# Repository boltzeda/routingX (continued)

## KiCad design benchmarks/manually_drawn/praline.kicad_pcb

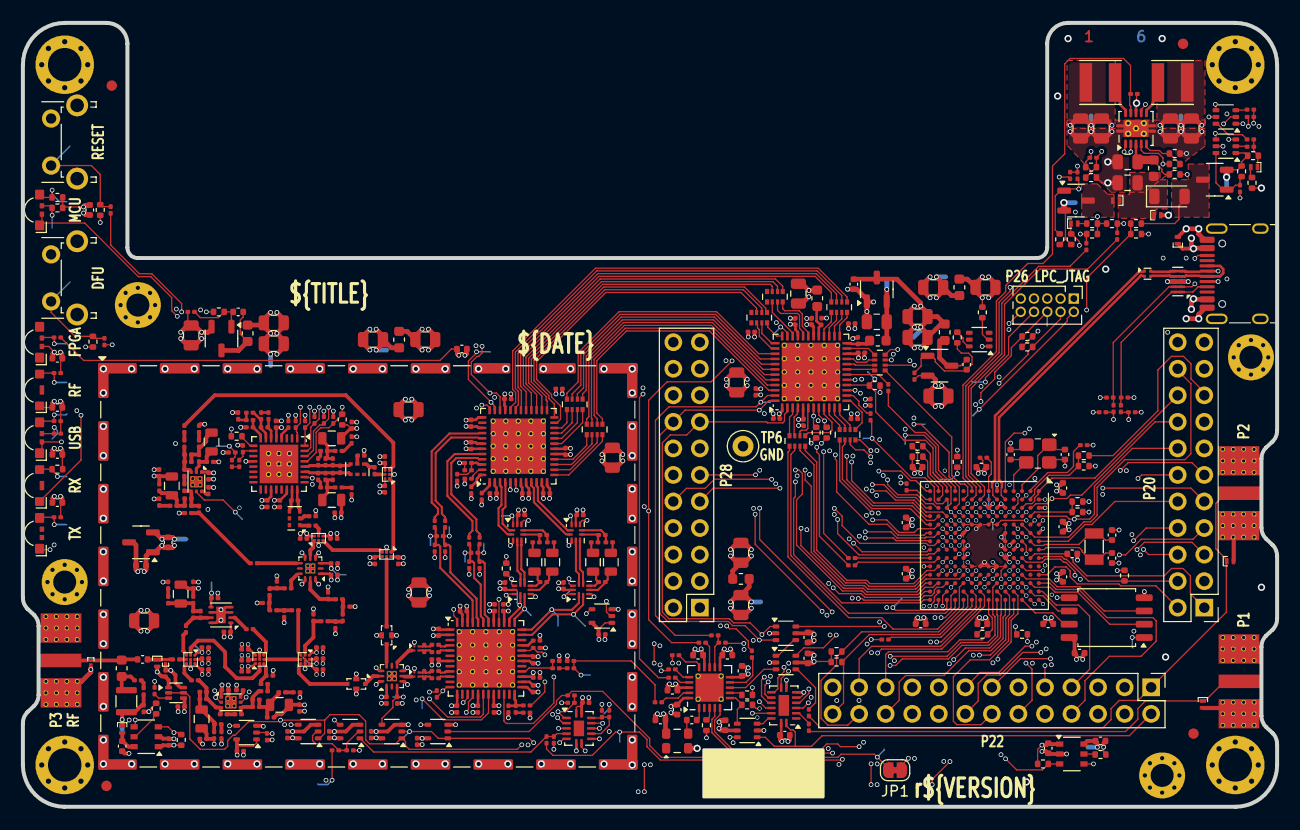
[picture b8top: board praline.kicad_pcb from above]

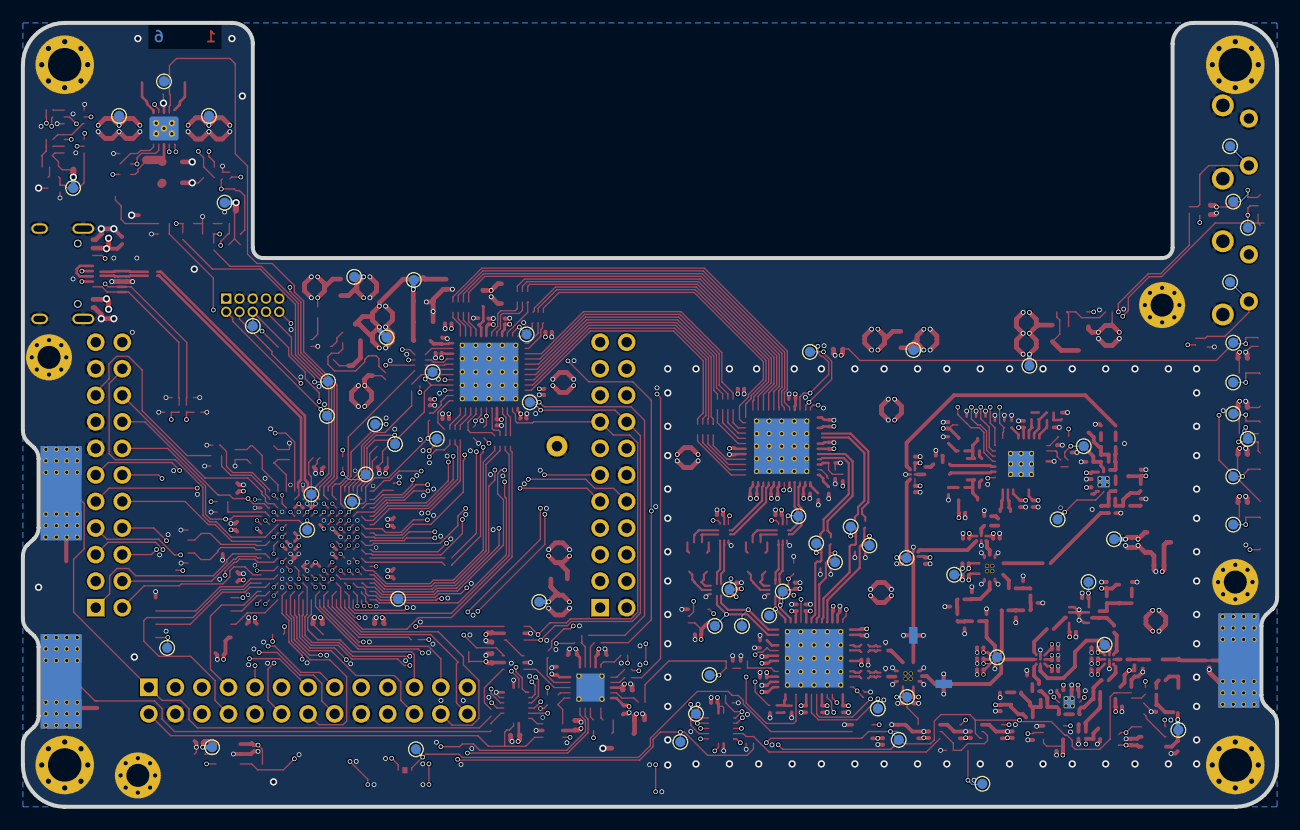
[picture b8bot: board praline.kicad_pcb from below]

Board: 6 copper layers, 120.0 x 75.0 mm, 581 parts (65 on the bottom side), 430 nets.

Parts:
C1, C2, C3, C5, C7, C8, C10, C17, C21, C24, C25, C26, C27, C28, C30, C31, C41, C42, C46, C48, C49, C50, C52, C53, C58, C59, C60, C62, C66, C68, C69, C71, C72, C73, C75, C77, C78, C79, C82, C83, C84, C85, C86, C87, C88, C89, C90, C92, C93, C94, C95, C97, C98, C100, C106, C123, C139, C141, C142, C148, C149, C150, C156, C159, C160, C161, C174, C176, C177, C178, C179, C183, C185, C187, C189, C190, C191, C192, C193, C194, C195, C196, C202, C203, C205, C206, C207, C208, C210, C211, C212: 1 uF; C_0201_0603Metric
C4, C6, C9, C11, C16, C18, C19, C20, C29, C55, C57, C63, C65: 3.3 nF; C_0201_0603Metric
C12, C13, C151, C152: 330 pF; C_0201_0603Metric
C14: 8.2 pF; C_0201_0603Metric
C15, C74, C76, C107, C108: 180 pF; C_0201_0603Metric
C22, C23, C32, C33, C39, C40, C43, C64, C80, C81, C110, C113, C119, C120, C121, C122, C124, C128, C129, C130, C131, C132, C133, C134, C135, C136, C137, C138, C140, C144, C162, C168, C171, C173, C199: 1 uF; C_0402_1005Metric
C34, C35, C36, C37, C67, C109, C125: 33 pF; C_0201_0603Metric
C44, C70, C112: 100 pF; C_0201_0603Metric
C45: 2.2 nF; C_0201_0603Metric
C47: 68 pF; C_0201_0603Metric
C51, C61, C101, C103, C198: 0.7 pF; C_0201_0603Metric
C54, C56: 1.8 pF; C_0201_0603Metric
C91, C96: 1.6 pF; C_0201_0603Metric
C99, C102, C115: 22 pF; C_0201_0603Metric
C104, C111: 4.3 pF; C_0201_0603Metric
C105, C117, C126, C127, C145, C146, C154, C163, C165, C166, C167, C169, C170, C172, C175, C181, C182, C184, C186, C197, C200, C201, C204: 10 uF; C_0805_2012Metric
C114, C188, C209: 0.3 pF; C_0201_0603Metric
C116: 47 pF; C_0201_0603Metric
C118, C157, C158, C164: 18 pF; C_0402_1005Metric
C143, C147: 22 uF; C_0805_2012Metric
C153, C155, C180: 100 nF; C_0402_1005Metric
D1: TVS; TSSLP-2-1
D2, D5: LED; LED_Single_Xinglight_XL-3210_Horizontal
D3, D9, D18: TVS; TSLP-2-19
D4, D6, D7, D8: LED; LED_Dual_Xinglight_XL-3210_Horizontal
D10: Schottky; TSLP-2-19
D11: 6.2 V; TSLP-2-19
D12: D; D_SOD-123FL
D13: 0; TSLP-2-19
D14: PIN; TSLP-2-19
D15: Schottky; TSSLP-2-1
D16, D17: 5.6 V; TSLP-2-19
FB1, FB2, FB3, FB4, FB5, FB6, FB7, FB8: Ferrite; L_0603_1608Metric
FID1, FID2, FID3, FID4: Fiducial_1mm_Mask2mm
FL1: CommonModeChoke; L_CommonModeChoke_Murata_DLM0NS
FL2, FL3: BPF; Filter_Pulse_BPF1608LM09R5000A
H1, H2, H3, H4: MountingHole_Pad; MountingHole_3.2mm_M3_Pad_Via
H5, H6, H7, H8: MountingHole_Pad; MountingHole_2.2mm_M2_Pad_Via
J1: USB_C; USB_C_Receptacle_HRO_TYPE-C-31-M-12
J3: RF_SHIELD_FRAME; Laird_Technologies_BMI-S-230-F_50.8x38.1mm
JP1: SolderJumper_2_Bridged; SolderJumper-2_P1.3mm_Bridged_RoundedPad1.0x1.5mm
L1, L7: DNP; L_0201_0603Metric
L2, L4, L5, L21, L22, L23, L24, L26, L27, L29, L33: 100 uH; L_TDK_MLZ2012_h1.25mm
L3, L12, L30, L31, L32: 56 nH; L_0201_0603Metric
L6, L14: 5.6 nH; L_0201_0603Metric
L8, L15: 4.7 nH; L_0201_0603Metric
L9: 10 nH; L_0201_0603Metric
L10, L11: 4.7 uH; L_Taiyo-Yuden_NR-40xx
L13: 2.2 uH; L_0603_1608Metric
L16, L17: 1.8 nH; L_0201_0603Metric
L18: 1.6 nH; L_0201_0603Metric
L19: 47 uH; L_Taiyo-Yuden_A251818
L28: 18 nH; L_0201_0603Metric
L34: 33 nH; L_0201_0603Metric
P1, P2, P3: SMA; SMA_MyAntenna_A-SMA-KE-16.5A_EdgeMount
P20, P28: HEADER_2x11; PinSocket_2x11_P2.54mm_Vertical_Flipped
P22: HEADER_2x13; PinSocket_2x13_P2.54mm_Vertical_Flipped
P26: LPC_JTAG; PinHeader_2x05_P1.27mm_Vertical
Q1: NMOS/PMOS; SOT-563
Q3, Q4, Q5, Q6: PMOS; SOT-23-3
Q7, Q10: 2NPN; SOT-363_SC-70-6
Q9: 2PNP; SOT-363_SC-70-6
R1, R2, R72, R115, R116, R117, R132, R137: 470; R_0201_0603Metric
R3, R11, R18, R61: 22.6k; R_0201_0603Metric
R4: 51k; R_0201_0603Metric
R5, R7, R36, R37, R40, R44, R48, R49, R50, R52, R59, R62, R63, R64, R66, R67, R68, R75, R85, R93, R100, R104, R105, R113, R120: 10k; R_0402_1005Metric
R6, R21, R29, R127, R140, R141, R143, R145, R148: 100; R_0201_0603Metric
R8, R9, R10, R13, R149, R150: 0; R_0201_0603Metric
R12, R19, R23, R30, R31, R32, R34, R41, R84, R108, R139, R142: 33; R_0201_0603Metric
R14, R15, R16, R17, R118, R119: DNP; R_0201_0603Metric
R20, R38, R46, R47, R55: 180k; R_0402_1005Metric
R22, R57, R81, R83, R86, R87: 33k; R_0201_0603Metric
R24, R35, R94, R96, R98, R114, R129, R133, R138, R144, R151, R153, R154: 1k; R_0201_0603Metric
R25: 750; R_0201_0603Metric
R26: 1.2k; R_0201_0603Metric
R27, R28, R45, R53: 1.8k; R_0402_1005Metric
R33, R123, R155: 10; R_0201_0603Metric
R39: 37.4k; R_0402_1005Metric
R42, R43, R124, R128, R130, R131, R136, R146, R147: 220; R_0201_0603Metric
R51, R54, R74, R76, R92, R95, R97, R99, R103, R106, R107, R109, R122, R126: 4.7k; R_0201_0603Metric
R56, R58, R70: 820k; R_0402_1005Metric
R60, R71, R79, R80: 5.1k; R_0402_1005Metric
R65, R82: 18k; R_0402_1005Metric
R69, R121, R125, R135: 12k; R_0201_0603Metric
R73: 3k; R_0402_1005Metric
R77, R78: 2.2k; R_0201_0603Metric
R88, R89, R90, R91: 18.7k; R_0402_1005Metric
R101: 100k; R_0402_1005Metric
R102, R110, R111, R112, R156, R157: 330; R_0201_0603Metric
R134: 180; R_0201_0603Metric
R152: 3; R_0201_0603Metric
RN1, RN2, RN3, RN4, RN5, RN6, RN7, RN8: 100; R_Array_Convex_4x0402
SW1, SW2: SWITCH; SW_Tactile_SPST_Angled_PTS645Vx58-2LFS
T1, T2: RF_BALUN; Anaren_0805_2012Metric-6
T3, T4: IF_BALUN; Balun_TDK_TFSZ06052460-3310A2X
TP1, TP2, TP3, TP4, TP5, TP7, TP8, TP9, TP10, TP11, TP12, TP13, TP14, TP15, TP16, TP17, TP18, TP19, TP20, TP21, TP22, TP23, TP24, TP25, TP26, TP27, TP28, TP29, TP30, TP31, TP32, TP33, TP34, TP35, TP36, TP37, TP38, TP39, TP40, TP41, TP42, TP43, TP44, TP45, TP46, TP47, TP48, TP49, TP50, TP51, TP52, TP53, TP54, TP55, TP56, TP57, TP58, TP59, TP60, TP61, TP62, TP63, TP64, TP65, TP66: TestPoint; TestPoint_Pad_D1.0mm
TP6: TestPoint; TestPoint_Loop_D1.80mm_Drill1.0mm_Beaded
U1, U2: MXD8546F; QFN-12-1EP_2x2mm_P0.5mm_EP1x1mm
U3, U8, U34, U35: GT4227; GTIC_UQFN-10_1.4x1.8mm_P0.4mm
U4: RFFC5072; QFN-32-1EP_5x5mm_P0.5mm_EP3.7x3.7mm_ThermalVias
U5, U6, U7: FM8625H; TSLP-6-4_1.1x0.7mm_P0.4mm
U9, U12, U14: MXD8638C
U10, U11, U13, U36: 74LVC1G86; SOT-353_SC-70-5
U15: TVS_USB; Diodes_UDFN-10_1.0x2.5mm_P0.5mm
U16: ICE40UP5K; QFN-48-1EP_7x7mm_P0.5mm_EP5.6x5.6mm_ThermalVias
U17: MAX2831; QFN-48-1EP_7x7mm_P0.5mm_EP5.6x5.6mm_ThermalVias
U18: MAX5865; QFN-48-1EP_7x7mm_P0.5mm_EP5.3x5.3mm_ThermalVias
U19: SI5351C; QFN-20-1EP_4x4mm_P0.5mm_EP2.7x2.7mm_ThermalVias
U20: W25Q32; SOIC-8_5.3x5.3mm_P1.27mm
U21: TPS62410; Texas_S-PVSON-N10_ThermalVias
U22, U32: LDO_2V5; SOT-23-3
U23: LPC4330FET180; TFBGA-180_12x12mm_Layout14x14_P0.8mm
U24, U28: AP22652; TSOP-6_1.65x3.05mm_P0.95mm
U25: TRF37C73; WSON-8-1EP_2x2mm_P0.5mm_EP0.9x1.6mm
U26: 74HC00; DHVQFN-14-1EP_2.5x3mm_P0.5mm_EP1x1.5mm
U27: 74LVC1G32; SOT-353_SC-70-5
U30, U31, U37: 74LVC1G3157; SOT-363_SC-70-6
U33: 74HC4051; DHVQFN-16-1EP_2.5x3.5mm_P0.5mm_EP1x2mm
U38, U40: BGB741L7ESD; TSLP-7-1
U39: 74LVC1G08; SOT-353_SC-70-5
X1: TCXO; Oscillator_SMD_SeikoEpson_TG2520SMN-xxx-xxxxxx-4Pin_2.5x2.0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
X2: MCU_XTAL; Crystal_SMD_3225-4Pin_3.2x2.5mm
X3: RTC_XTAL; Crystal_SMD_3215-2Pin_3.2x1.5mm

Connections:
1V2FPGA: C117.1, C178.1, C179.1, C184.1, C196.1, C205.1, FB6.2, FB7.2, TP22.1, U16.5 (VCC), U16.30 (VCC)
2V5FPGA: C177.1, FB8.2, U16.24 (VPP_2V5)
2V5RF: C7.1, C8.1, C10.1, C17.1, C21.1, C23.1, C24.1, C26.1, C27.1, C30.1, C31.1, C60.1, C66.1, C95.1, Q1.4 (S), TP3.1, U1.1 (VDD), U2.1 (VDD), U5.4 (VDD), U6.4 (VDD), U7.4 (VDD), U9.7 (VDD), U10.5 (VCC), U11.5 (VCC), U12.7 (VDD), U14.7 (VDD), U26.1, U26.4, U26.14 (VCC), U27.5 (VCC), U32.2 (VO)
3V3AUX: C32.1, P20.3, P22.11, P28.1, TP17.1, U28.6 (OUT)
3V3CLK: C113.1, C119.1, C120.1, C121.1, C122.1, C167.1, C168.2, C199.1, FB2.2, R104.1, R105.1, TP16.1, U19.10 (VDDOB), U19.11 (VDDOA), U19.14 (VDDOD), U19.18 (VDDOC), U19.20 (VDD), U37.5 (V+), X1.4 (Vcc)
3V3FPGA: C123.1, C140.1, C148.1, C149.1, C150.1, C166.1, C173.1, C174.1, C181.1, C182.1, C183.1, C185.1, C186.1, C187.1, C197.1, FB2.1, FB4.2, R44.2, R45.2, R76.2, TP2.1, U16.1 (VCCIO_2), U16.22 (SPI_VCCIO1), U16.33 (VCCIO_0), U18.18 (OVDD), U22.3 (VI)
3V3LED: C80.1, C81.1, C110.1, C124.1, C163.1, C170.1, FB5.2, Q3.2 (S), R11.1, R49.1, R50.2, R72.2, R73.2, R74.2, R75.2, R125.2, SW1.2, TP15.1
!VAA_ENABLE: R60.2, U23.G4 (P8_1)
+1V2: C125.1, C126.1, C127.1, C172.1, FB7.1, L10.2, R47.1, R53.1, TP18.1
+2V5: C175.1, FB8.1, TP1.1, U22.2 (VO)
+5V: C147.1, FB1.1, R52.1, U21.3 (VIN)
/ADC, DAC/AA_BYPASS_I+: U34.4 (D1-), U35.7 (D2+)
/ADC, DAC/AA_BYPASS_I-: U34.5 (D1+), U35.6 (D2-)
/ADC, DAC/AA_BYPASS_Q+: U3.6 (D2-), U8.5 (D1+)
/ADC, DAC/AA_BYPASS_Q-: U3.7 (D2+), U8.4 (D1-)
/ADC, DAC/AA_EN: TP55.1, U8.10 (S), U23.K7 (P1_14), U34.10 (S), U36.2
/ADC, DAC/AFE_CLK: R31.1, TP29.1, U16.35 (IOT_46b_G0), U18.6 (CLK)
/ADC, DAC/COM: C97.1, U18.47 (COM)
/ADC, DAC/DA0: RN5.8 (R1.2), U18.13 (DA0)
/ADC, DAC/DA1: RN5.7 (R2.2), U18.14 (DA1)
/ADC, DAC/DA2: RN5.6 (R3.2), U18.15 (DA2)
/ADC, DAC/DA3: RN5.5 (R4.2), U18.16 (DA3)
/ADC, DAC/DA4: RN4.8 (R1.2), U18.19 (DA4)
/ADC, DAC/DA5: RN4.7 (R2.2), U18.20 (DA5)
/ADC, DAC/DA6: RN4.6 (R3.2), U18.21 (DA6)
/ADC, DAC/DA7: RN4.5 (R4.2), U18.22 (DA7)
/ADC, DAC/DD0: RN3.7 (R2.2), U18.23 (DD0)
/ADC, DAC/DD1: RN3.6 (R3.2), U18.24 (DD1)
/ADC, DAC/DD2: RN3.5 (R4.2), U18.25 (DD2)
/ADC, DAC/DD3: RN2.7 (R2.2), U18.26 (DD3)
/ADC, DAC/DD4: RN2.6 (R3.2), U18.27 (DD4)
/ADC, DAC/DD5: RN2.5 (R4.2), U18.28 (DD5)
/ADC, DAC/DD6: RN1.8 (R1.2), U18.29 (DD6)
/ADC, DAC/DD7: RN1.7 (R2.2), U18.30 (DD7)
/ADC, DAC/DD8: RN1.6 (R3.2), U18.31 (DD8)
/ADC, DAC/DD9: RN1.5 (R4.2), U18.32 (DD9)
/ADC, DAC/IA+: U18.3 (IA+), U34.2 (D-)
/ADC, DAC/IA-: U18.4 (IA-), U34.1 (D+)
/ADC, DAC/ID+: R13.1, U18.45 (ID+)
/ADC, DAC/ID-: R10.1, U18.44 (ID-)
/ADC, DAC/QA+: U8.1 (D+), U18.10 (QA+)
/ADC, DAC/QA-: U8.2 (D-), U18.9 (QA-)
/ADC, DAC/QD+: R8.1, U18.40 (QD+)
/ADC, DAC/QD-: R9.1, U18.41 (QD-)
/ADC, DAC/REFN: C98.1, U18.48 (REFN)
/ADC, DAC/REFP: C100.1, U18.1 (REFP)
/ADC, DAC/RXBB.I+: TP62.1, U17.38 (RXBBI+), U35.1 (D+)
/ADC, DAC/RXBB.I-: TP63.1, U17.37 (RXBBI-), U35.2 (D-)
/ADC, DAC/RXBB.Q+: TP60.1, U3.1 (D+), U17.36 (RXBBQ+)
/ADC, DAC/RXBB.Q-: TP61.1, U3.2 (D-), U17.35 (RXBBQ-)
/ADC, DAC/TXBB.I+: R8.2, R17.1, R119.2, TP57.1, U17.45 (TXBBI+)
/ADC, DAC/TXBB.I-: R9.2, R16.1, R119.1, TP56.1, U17.44 (TXBBI-)
/ADC, DAC/TXBB.Q+: R10.2, R15.1, R118.2, TP58.1, U17.43 (TXBBQ+)
/ADC, DAC/TXBB.Q-: R13.2, R14.1, R118.1, TP59.1, U17.42 (TXBBQ-)
/ADC, DAC/~AA_EN: TP54.1, U3.10 (S), U35.10 (S), U36.4
/ADC, DAC/~BB_EN: R113.1, U3.8 (~OE), U8.8 (~OE), U34.8 (~OE), U35.8 (~OE)
/Clock Generator/AUX_CLK1: R84.1, U33.14 (A1)
/Clock Generator/AUX_CLK2: P22.25, R34.1, U33.4 (A7)
/Clock Generator/CLK0: R31.2, U19.13 (CLK0)
/Clock Generator/CLK1: R12.2, R41.2, U19.12 (CLK1)
/Clock Generator/CLK2: R139.2, U19.9 (CLK2)
/Clock Generator/CLK3: U19.8 (CLK3), U31.3
/Clock Generator/CLK4: R32.2, U19.19 (CLK4)
/Clock Generator/CLK5: R23.2, U19.17 (CLK5)
/Clock Generator/CLK6: R84.2, U19.16 (CLK6)
/Clock Generator/CLK7: R34.2, U19.15 (CLK7)
/Clock Generator/CLKIN: R85.2, U19.6 (CLKIN), U37.4
/Clock Generator/CLKIN_CTRL: U23.J10 (P1_20), U37.6
/Clock Generator/FPGA_CLK: R12.1, TP65.1, U16.47 (IOB_2a)
/Clock Generator/INTR: R104.2, U19.3 (INTR)
/Clock Generator/MCU_CLK: R139.1, TP36.1, U23.F4 (P4_7)
/Clock Generator/MIX_CLK: R23.1, R150.2, R151.1, TP34.1
/Clock Generator/OEB: R105.2, U19.7 (OEB)
/Clock Generator/P1: D3.1 (K), P1.1 (RF), R33.2
/Clock Generator/P1_CLKIN: U33.15 (A2), U37.3
/Clock Generator/P1_CTRL0: U23.F14 (P2_10), U33.11 (S0)
/Clock Generator/P1_CTRL1: U23.F12 (P6_8), U33.10 (S1)
/Clock Generator/P1_CTRL2: U23.H13 (P6_9), U33.9 (S2)
/Clock Generator/P2: D9.1 (K), P2.1 (RF), P22.1, R108.1
/Clock Generator/P2_5: U23.J12 (P2_5), U33.5 (A5)
/Clock Generator/P2_CTRL0: U23.K10 (PE_3), U30.6
/Clock Generator/P2_CTRL1: U23.J11 (PE_4), U31.6
/Clock Generator/P22_CLKIN: P22.2, U33.1 (A4), U37.1
/Clock Generator/SCT_CLK: R41.1, TP32.1, U23.M14 (P6_4)
/Clock Generator/TRIGGER.IN: P28.16, R127.1, U16.48 (IOB_4a), U30.3, U33.13 (A0)
/Clock Generator/TRIGGER.OUT: P28.15, R6.2, U16.2 (IOB_6a), U30.1, U33.12 (A3)
/Clock Generator/XA: C155.1, U19.1 (XA)
/Clock Generator/XCVR_CLK: R32.1, R148.1, R149.2, TP33.1
/FPGA/CAPTURE_EN: RN7.3 (R3.1), U16.11 (IOB_20a)
/FPGA/DIRECTION: RN7.2 (R2.1), U16.12 (IOB_22a)
/FPGA/DISABLE: RN8.1 (R1.1), U16.23 (IOT_37a)
/FPGA/FPGA_CONFIG.CDONE: R45.1, TP48.1, U16.7 (CDONE), U23.L3 (P4_10)
/FPGA/FPGA_CONFIG.~CRESET: R40.1, TP50.1, U16.8 (~CRESET), U23.M3 (P5_2)
/FPGA/FPGA_CONFIG.~SPI_CS: R44.1, TP49.1, U16.16 (IOB_35b_SPI_SS), U23.M1 (P5_1)
/FPGA/FPGA_DA0: RN5.1 (R1.1), U16.46 (IOB_0a)
/FPGA/FPGA_DA1: RN5.2 (R2.1), U16.45 (IOB_5b)
/FPGA/FPGA_DA2: RN5.3 (R3.1), U16.44 (IOB_3b_G6)
/FPGA/FPGA_DA3: RN5.4 (R4.1), U16.43 (IOT_49a)
/FPGA/FPGA_DA4: RN4.1 (R1.1), U16.42 (IOT_51a)
/FPGA/FPGA_DA5: RN4.2 (R2.1), U16.41 (RGB2)
/FPGA/FPGA_DA6: RN4.3 (R3.1), U16.40 (RGB1)
/FPGA/FPGA_DA7: RN4.4 (R4.1), U16.39 (RGB0)
/FPGA/FPGA_DD0: RN3.2 (R2.1), U16.38 (IOT_50b)
/FPGA/FPGA_DD1: RN3.3 (R3.1), U16.37 (IOT_45a_G1)
/FPGA/FPGA_DD2: RN3.4 (R4.1), U16.36 (IOT_48b)
/FPGA/FPGA_DD3: RN2.2 (R2.1), U16.34 (IOT_44b)
/FPGA/FPGA_DD4: RN2.3 (R3.1), U16.32 (IOT_43a)
/FPGA/FPGA_DD5: RN2.4 (R4.1), U16.31 (IOT_42b)
/FPGA/FPGA_DD6: RN1.1 (R1.1), U16.28 (IOT_41a)
/FPGA/FPGA_DD7: RN1.2 (R2.1), U16.27 (IOT_38b)
/FPGA/FPGA_DD8: RN1.3 (R3.1), U16.26 (IOT_39a)
/FPGA/FPGA_DD9: RN1.4 (R4.1), U16.25 (IOT_36b)
/FPGA/FPGA_SGPIO0: RN8.2 (R2.1), U16.21 (IOB_23b)
/FPGA/FPGA_SGPIO1: RN8.4 (R4.1), U16.19 (IOB_29b)
/FPGA/FPGA_SGPIO2: RN6.2 (R2.1), U16.6 (IOB_13b)
/FPGA/FPGA_SGPIO3: RN7.1 (R1.1), U16.13 (IOB_24a)
/FPGA/FPGA_SGPIO4: RN7.4 (R4.1), U16.10 (IOB_18a)
/FPGA/FPGA_SGPIO5: RN6.4 (R4.1), U16.3 (IOB_9b)
/FPGA/FPGA_SGPIO6: RN6.3 (R3.1), U16.4 (IOB_8a)
/FPGA/FPGA_SGPIO7: R21.1, U16.18 (IOB_31b)
/FPGA/FPGA_SGPIO8: RN8.3 (R3.1), U16.20 (IOB_25b_G3)
/FPGA/Q_INVERT: RN6.1 (R1.1), U16.9 (IOB_16a)
/FPGA/SGPIO0: RN8.7 (R2.2), U23.K3 (P0_0)
/FPGA/SGPIO1: RN8.5 (R4.2), U23.K2 (P0_1)
/FPGA/SGPIO2: RN6.7 (R2.2), U23.P11 (P1_15)
/FPGA/SGPIO3: RN7.8 (R1.2), U23.L5 (P1_16)
/FPGA/SGPIO4: RN7.5 (R4.2), U23.M8 (P9_4)
/FPGA/SGPIO5: RN6.5 (R4.2), U23.K12 (P6_6)
/FPGA/SGPIO6: RN6.6 (R3.2), U23.L13 (P2_2)
/FPGA/SGPIO7: R21.2, U23.L1 (P1_0)
/FPGA/SGPIO8: RN8.6 (R3.2), U23.E4 (P8_0)
/FPGA/SGPIO9: RN7.6 (R3.2), U23.P5 (P9_3)
/FPGA/SGPIO10: RN8.8 (R1.2), U23.J4 (P8_2)
/FPGA/SGPIO11: RN7.7 (R2.2), U23.L6 (P1_17)
/FPGA/SGPIO12: RN6.8 (R1.2), U23.N10 (P1_18)
/FPGA/VCCPLL: C176.1, FB6.1, U16.29 (VCCPLL)
/IF Transceiver/CPOUT: C44.2, R25.2, R26.2, U17.24 (CPOUT)
/IF Transceiver/IF: FL3.3 (OUT), U7.5 (RFIN)
/IF Transceiver/MIX_BYPASS: FL2.3 (OUT), U9.5 (RF2)
/IF Transceiver/RXIF: T3.2, U2.7 (RF1)
/IF Transceiver/RXIF+: C99.1, U17.4 (RXRF+)
/IF Transceiver/RXIF-: C102.1, U17.5 (RXRF-)
/IF Transceiver/RXIF_BALUN+: C102.2, L7.1, T3.3
/IF Transceiver/RXIF_BALUN-: C99.2, L7.2, T3.4
/IF Transceiver/RX_EN: C9.2, C16.2, C20.2, Q1.2 (G), Q1.5 (G), TP35.1, U5.6 (CTRL), U6.6 (CTRL), U7.6 (CTRL), U10.1, U11.1, U26.3, U26.9
/IF Transceiver/RX_MIX_OUT: U5.1 (RF2), U7.1 (RF2)
/IF Transceiver/RX_XOR_MIX: C18.2, TP39.1, U2.3 (V1), U10.4
/IF Transceiver/TUNE: C47.2, R25.1, U17.32 (TUNE)
/IF Transceiver/TXIF: T4.2, U2.5 (RF2)
/IF Transceiver/TXIF+: C104.1, U17.9 (TXRF+)
/IF Transceiver/TXIF-: C111.1, U17.10 (TXRF-)
/IF Transceiver/TXIF_BALUN+: C111.2, L9.1, T4.3
/IF Transceiver/TXIF_BALUN-: C104.2, L9.2, T4.4
/IF Transceiver/TX_MIX_IN: U6.3 (RF1), U7.3 (RF1)
/IF Transceiver/XCVR.LD: U17.22 (LD), U23.M9 (P9_6)
/IF Transceiver/XCVR.RSSI: U17.16 (RSSI), U23.C4 (ADC0_1/ADC1_1)
/IF Transceiver/XCVR.RXHP: U17.40 (RXHP), U23.P13 (PD_15)
/IF Transceiver/XCVR.RXTX: U17.48 (RXTX), U23.L12 (PE_2)
/IF Transceiver/XCVR.~CS: U17.15 (~CS), U23.L11 (PD_14)
/IF Transceiver/XCVR.~SHDN: R109.1, U17.12 (~SHDN), U23.M12 (PE_1)
/IF Transceiver/XTAL: C115.2, C116.1, U17.28 (XTAL)
/Image Reject Filters/LPF_OR_MIX_BYPASS: C19.2, TP40.1, U9.8 (V2), U27.4
/Image Reject Filters/MIX_EN: C29.2, TP37.1, U9.1 (V1), U10.2, U26.6, U39.1
/Image Reject Filters/RF: U9.4 (ANT), U12.4 (ANT)
/Image Reject Filters/RX_MIX_IN: U1.5 (RF2), U6.1 (RF2)
/Image Reject Filters/RX_XOR_LPF: C11.2, TP38.1, U1.3 (V1), U11.4
/Image Reject Filters/TX_MIX_OUT: C189.1, U1.7 (RF1)
/Microcontroller/1V2_EN: R54.2, U21.9 (EN2), U23.J1 (P8_7)
/Microcontroller/ADC0_0: P20.20, U23.B6 (ADC0_0/ADC1_0/DAC), U23.C5 (PB_6)
/Microcontroller/ADC0_2: P20.16, U23.B3 (ADC0_2/ADC1_2), U23.C2 (P4_5)
/Microcontroller/ADC0_3: R38.2, R39.1, U23.B4 (ADC0_3/ADC1_3)
/Microcontroller/ADC0_4: R106.1, R157.1, U23.A5 (ADC0_4/ADC1_4)
/Microcontroller/ADC0_5: P20.18, U23.A1 (P4_4), U23.C3 (ADC0_5/ADC1_5)
/Microcontroller/ADC0_6: P20.14, U23.A4 (ADC0_6/ADC1_6), U23.D6 (PF_4)
/Microcontroller/ADC0_7: R103.1, R156.1, U23.B5 (ADC0_7/ADC1_7)
/Microcontroller/CPLD_TCK: P28.17, U23.P14 (P6_1)
/Microcontroller/DBGEN: R64.1, TP24.1, U23.K4 (DBGEN)
/Microcontroller/GPIO3_8: P20.5, U23.B14 (P7_0)
/Microcontroller/GPIO3_9: P20.6, U23.C13 (P7_1)
/Microcontroller/GPIO3_10: P20.7, U23.A14 (P7_2)
/Microcontroller/GPIO3_11: P20.8, U23.C12 (P7_3)
/Microcontroller/GPIO3_12: P20.9, U23.C6 (P7_4)
/Microcontroller/GPIO3_13: P20.10, U23.A7 (P7_5)
/Microcontroller/GPIO3_14: P20.11, U23.F5 (P7_6)
/Microcontroller/GPIO3_15: P20.12, U23.D5 (P7_7)
/Microcontroller/I2C1_SCL: P22.5, U23.L9 (P2_4)
/Microcontroller/I2C1_SDA: P22.6, U23.G11 (P2_3)
/Microcontroller/I2S0_RX_SDA: P28.19, U23.K11 (P6_2)
/Microcontroller/I2S0_RX_WS: P22.15, U23.D10 (P3_1)
/Microcontroller/I2S0_TX_MCLK: P22.17, U23.P10 (CLK2)
/Microcontroller/I2S0_TX_SCK: P22.16, U23.D12 (P3_0)
/Microcontroller/I2S0_TX_SDA: P22.13, U23.D9 (P3_2)
/Microcontroller/ISP: R59.2, U23.G12 (P2_7)
/Microcontroller/LPF_EN: R98.1, TP45.1, U23.H12 (PA_1)
/Microcontroller/MIXER.ENBL: C109.1, U4.1 (ENBL/GPO5), U23.P1 (P9_0)
/Microcontroller/MIXER.LD: U4.26 (GPO4/LD/DO), U23.M7 (PD_11)
/Microcontroller/MIXER.SCLK: C36.1, U4.31 (SCLK), U23.L7 (P9_5)
/Microcontroller/MIXER.SDATA: C37.1, U4.32 (SDATA), U23.M6 (P9_2)
/Microcontroller/MIXER.~EN: C35.1, U4.30 (~EN), U23.N7 (P5_4)
/Microcontroller/MIXER.~RESET: C34.1, R5.2, U4.29 (~RESET), U23.N8 (P5_5)
/Microcontroller/MODE: R51.1, U21.2 (MODE/DATA), U23.J2 (P4_9)
/Microcontroller/P1_1: R67.1, U23.N1 (P1_1)
/Microcontroller/P1_2: R68.1, U23.N2 (P1_2)
/Microcontroller/P1_7: P28.22, U23.N4 (P1_7)
/Microcontroller/P2_8: P22.23, R30.1, U23.H14 (P2_8)
/Microcontroller/P2_9: P22.21, R93.1, U23.G14 (P2_9)
/Microcontroller/P2_13: P22.22, U23.E14 (P2_13)
/Microcontroller/P5_3: P28.21, U23.P6 (P5_3)
/Microcontroller/P5_6: P28.13, U23.M11 (P5_6)
/Microcontroller/P5_7: P28.14, U23.N11 (P5_7)
/Microcontroller/P9_1: P28.20, U23.P4 (P9_1)
/Microcontroller/PA_3: P22.12, U23.E10 (PA_3)
/Microcontroller/PA_4: P22.9, U23.E12 (PA_4)
/Microcontroller/PB_0: P22.14, U23.D14 (PB_0)
/Microcontroller/PB_1: P22.7, U23.A13 (PB_1)
/Microcontroller/PB_3: P22.8, U23.A12 (PB_3)
/Microcontroller/PB_5: P20.2, U23.A11 (PB_5)
/Microcontroller/PE_0: P28.18, U23.N12 (PE_0)
/Microcontroller/RF_AMP_EN: R96.1, TP46.1, U23.J13 (PA_2)
/Microcontroller/RREF: R69.1, U23.G1 (USB0_RREF)
/Microcontroller/RTCX1: C118.1, U23.A8 (RTCX1), X3.2
/Microcontroller/RTCX2: C164.1, U23.B7 (RTCX2), X3.1
/Microcontroller/SD_CD: P28.3, U23.L8 (P1_13)
/Microcontroller/SD_CLK: P28.11, U23.M4 (CLK0)
/Microcontroller/SD_CMD: P28.9, U23.P3 (P1_6)
/Microcontroller/SD_DAT0: P28.7, U23.N5 (P1_9)
/Microcontroller/SD_DAT1: P28.6, U23.N6 (P1_10)
/Microcontroller/SD_DAT2: P28.5, U23.P8 (P1_11)
/Microcontroller/SD_DAT3: P28.4, U23.P7 (P1_12)
/Microcontroller/SD_POW: P28.10, U23.N3 (P1_5)
/Microcontroller/SD_VOLT0: P28.8, U23.M5 (P1_8)
/Microcontroller/SPIFI_CIPO: U20.2 (DO/IO_{1}), U23.B12 (P3_6)
/Microcontroller/SPIFI_COPI: U20.5 (DI/IO_{0}), U23.C10 (P3_7)
/Microcontroller/SPIFI_SCK: U20.6 (CLK), U23.B13 (P3_3)
/Microcontroller/SPIFI_SIO2: U20.3 (~WP/IO_{2}), U23.C11 (P3_5)
/Microcontroller/SPIFI_SIO3: U20.7 (~HOLD/~RESET/IO_{3}), U23.C14 (P3_4)
/Microcontroller/SPIFI_~CS: TP64.1, U20.1 (~CS), U23.C9 (P3_8)
/Microcontroller/TCK: P26.4, R66.2, TP25.1, U23.G5 (TCK/SWDCLK)
/Microcontroller/TDI: P26.8, TP28.1, U23.H4 (TDI)
/Microcontroller/TDO: P26.6, R63.1, TP27.1, U23.J5 (TDO/SWO)
/Microcontroller/TMS: P26.2, TP26.1, U23.K5 (TMS/SWDIO)
/Microcontroller/TX_EN: JP1.2 (B), R24.1, TP43.1, U39.2
/Microcontroller/U0_RXD: P22.19, U23.M13 (P2_1)
/Microcontroller/U0_TXD: P22.20, U23.N14 (P2_0)
/Microcontroller/USB0_VBUS: R62.1, R65.2, U23.E1 (USB0_VBUS)
/Microcontroller/USB_DATA.D+: FL1.3, U23.E2 (USB0_DP)
/Microcontroller/USB_DATA.D-: FL1.1, U23.F2 (USB0_DM)
/Microcontroller/VBAT: C136.1, P20.1, U23.B9 (VBAT)
/Microcontroller/VBUSCTRL: P20.17, R37.2
/Microcontroller/VBUS_SAFE: D12.2 (A), Q4.3 (D), R62.2
/Microcontroller/WAKEUP: P20.4, R48.2, U23.A9 (WAKEUP0)
/Microcontroller/XTAL1: C157.1, U23.C1 (XTAL1), X2.1
/Microcontroller/XTAL2: C158.1, U23.D1 (XTAL2), X2.3
/Microcontroller/~3V3AUX_EN: R100.1, U23.H11 (P6_7), U28.3 (~EN)
/Microcontroller/~3V3AUX_OC: U23.F11 (P6_11), U28.4 (~OC)
/Microcontroller/~BIAS_EN: R36.1, U23.D13 (P2_12), U24.3 (~EN)
/Microcontroller/~BIAS_OC: U23.E13 (P2_11), U24.4 (~OC)
/Microcontroller/~LED1: D4.2 (K1), D4.4 (K2), U23.D3 (P4_1)
/Microcontroller/~LED2: D5.1 (K), U23.A2 (P4_2)
/Microcontroller/~LED3: D6.4 (K2), U23.F13 (P6_12)
/Microcontroller/~LED4: D7.2 (K1), D7.4 (K2), U23.J3 (P8_6)
/Microcontroller/~MIX_EN: R94.1, TP44.1, U23.N13 (P6_3)
/Microcontroller/~RESET: P22.3, P26.10, R19.1, U23.C7 (~RESET)
/Microcontroller/~TRST: TP5.1, U23.L4 (~TRST)
/Microcontroller/~VBUS_IN_EN: R77.2, U23.H2 (P8_4)
/Microcontroller/~VIN_IN_EN: R78.2, U23.H1 (P8_5)
/Mixer/MIX_IN: C28.2, U6.5 (RFIN)
/Mixer/MIX_IN+: L1.1, T1.4 (PR2), U4.23 (MIX_IPP)
/Mixer/MIX_IN-: L1.2, T1.3 (PR1), U4.24 (MIX_IPN)
/Mixer/MIX_OUT: C46.1, U5.5 (RFIN)
/Mixer/MIX_OUT+: C114.2, L3.2, L6.2, R124.2, T2.3 (PR1), U4.28 (MIX_OPP)
/Mixer/MIX_OUT-: C114.1, C198.1, L30.2, R43.2, T2.4 (PR2), U4.27 (MIX_OPN)
/Mixer/REF_IN: C67.2, C70.1, U4.10 (REF_IN)
/Mixer/TX_MIX_EN: TP66.1, U38.5 (CTRL), U39.4
/Power/VBUS: D18.1 (K), J1.A4 (VBUS), J1.A9 (VBUS), J1.B4 (VBUS), J1.B9 (VBUS), P20.21, Q4.2 (S), Q9.1 (E1), R58.1, R88.1, TP20.1
/Power/VIN: P20.22, Q5.2 (S), Q9.4 (E2), R70.1, R90.1, TP21.1
/RF Front End/AMP_BYPASS: U12.2 (RF3), U14.2 (RF3)
/RF Front End/BIAS: D10.1 (K), L19.1, R35.1, R126.2, TP47.1
/RF Front End/RX_AMP_EN: U13.4, U40.5 (CTRL)
/RF Front End/RX_AMP_IN: C58.1, U14.5 (RF2)
/RF Front End/RX_AMP_OUT: C50.1, C209.1, U12.3 (RF1)
/RF Front End/TX_AMP_IN: C59.1, U12.5 (RF2)
/RF Front End/TX_AMP_OUT: C62.2, U14.3 (RF1)
/RF Front End/~RX_AMP_EN: C6.2, C57.2, C65.2, TP41.1, U12.8 (V2), U13.2, U14.1 (V1), U26.8
/RF Front End/~TX_AMP_EN: C4.2, C55.2, C63.2, TP42.1, U12.1 (V1), U14.8 (V2), U25.5 (PWDN), U26.11
/USB/CC1: C152.1, J1.A5 (CC1), R106.2, U15.1, U15.10 (NC)
/USB/CC2: C151.1, J1.B5 (CC2), R103.2, U15.2, U15.9 (NC)
/USB/D+: FL1.4, J1.A6 (D+), J1.B6 (D+), U15.4, U15.7 (NC)
/USB/D-: FL1.2, J1.A7 (D-), J1.B7 (D-), U15.5, U15.6 (NC)
CS_AD: U18.36 (~CS), U23.P12 (PD_16)
GND: C1.2, C2.2, C3.2, C4.1, C5.2, C6.1, C7.2, C8.2, C9.1, C10.2, C11.1, C12.2, C13.2, C16.1, C17.2, C18.1, C19.1, C20.1, C21.2, C22.2, C23.2, C24.2, C25.2, C26.2, C27.2, C29.1, C30.2, C31.2, C32.2, C33.2, C34.2, C35.2, C36.2, C37.2, C39.2, C40.2, C41.2, C42.2, C43.2, C44.1, C45.1, C47.1, C48.2, C49.1, C51.2, C52.2, C53.2, C54.2, C55.1, C56.2, C57.1, C60.2, C61.2, C63.1, C65.1, C66.2, C69.2, C70.2, C71.2, C72.2, C73.2, C75.2, C77.2, C79.2, C80.2, C81.2, C82.2, C83.2, C84.2, C85.2, C86.2, C87.2, C88.2, C89.2, C90.2, C92.2, C93.2, C94.2, C95.2, C97.2, C98.2, C100.2, C105.2, C106.2, C109.2, C110.2, C113.2, C116.2, C117.2, C118.2, C119.2, C120.2, C121.2, C122.2, C123.2, C124.2, C126.2, C127.2, C128.2, C129.2, C130.2, C131.2, C132.2, C133.2, C134.2, C135.2, C136.2, C137.2, C138.2, C140.2, C141.2, C142.2, C143.2, C144.2, C145.1, C146.1, C147.2, C148.2, C149.2, C150.2, C151.2, C152.2, C154.2, C156.2, C157.2, C158.2, C159.2, C160.2, C161.2, C162.2, C163.2, C164.2, C165.2, C166.2, C167.2, C168.1, C169.2, C170.2, C171.2, C172.2, C173.2, C174.2, C175.2, C176.2, C177.2, C178.2, C179.2, C181.2, C182.2, C183.2, C184.2, C185.2, C186.2, C187.2, C188.2, C190.2, C193.2, C194.2, C196.2, C197.2, C199.2, C200.2, C201.2, C204.2, C205.2, C206.2, C208.2, C209.2, C212.2, D1.2 (A2), D2.1 (K), D3.2 (A), D8.2 (K1), D9.2 (A), D11.2 (A), D14.2 (A), D18.2 (A), FL2.2 (GND), FL2.4 (GND), FL3.2 (GND), FL3.4 (GND), H1.1, H2.1, H3.1, H4.1, H5.1, H6.1, H7.1, H8.1, J1.A1 (GND), J1.A12 (GND), J1.B1 (GND), J1.B12 (GND), J1.S1 (SHIELD), J3.1 (Shield), L16.2, L17.2, L18.2, P1.2 (GND), P2.2 (GND), P3.2 (GND), P20.13, P20.15, P20.19, P22.4, P22.10, P22.18, P26.3, P26.5, P26.9, P28.2, P28.12, Q1.1 (S), Q7.1 (E1), Q10.1 (E1), Q10.4 (E2), R4.1, R7.2, R14.2, R15.2, R16.2, R17.2, R20.2, R22.2, R39.2, R40.2, R42.1, R46.1, R51.2, R54.1, R55.1, R57.2, R65.1, R68.2, R69.2, R79.2, R80.2, R82.1, R85.1, R89.2, R91.2, R92.2, R93.2, R95.2, R97.2, R99.2, R101.2, R107.2, R109.2, R113.2, R122.2, R126.1, R130.1, R131.1, R136.1, R143.1, R146.1, R147.2, R148.2, R151.2, R156.2, R157.2, SW1.SH (B), SW2.2, SW2.SH (B), T3.1 (GND), T4.1 (GND), TP6.1, TP23.1, U1.4 (GND), U1.6 (GND), U1.10 (GND), U1.12 (GND), U1.13 (GND), U2.4 (GND), U2.6 (GND), U2.10 (GND), U2.12 (GND), U2.13 (GND), U3.3 (GND), U4.12 (TM), U4.33 (EP), U5.2 (GND), U6.2 (GND), U7.2 (GND), U8.3 (GND), U9.6 (GND), U9.9 (GND), U10.3 (GND), U11.3 (GND), U12.6 (GND), U12.9 (GND), U13.3 (GND), U14.6 (GND), U14.9 (GND), U15.3 (VSS), U15.8 (VSS), U16.49 (GND), U17.2 (GNDRXLNA), U17.26 (GNDCP), U17.31 (GNDVCO), U17.47 (GNDTEST), U17.49 (EP), U18.5 (GND), U18.7 (GND), U18.12 (GND), U18.17 (OGND), U18.37 (GND), U18.42 (GND), U18.49 (EP), U19.21 (GND), U20.4 (GND), U21.8 (GND), U21.11 (PAD), U22.1 (GND), U23.A3 (VSSA), U23.D7 (VSS), U23.E6 (VSS), U23.E7 (VSS), U23.E9 (VSS), U23.F1 (USB0_VSSA_REF), U23.F10 (VSS), U23.G3 (USB0_VSSA_TERM), U23.K6 (VSS), U23.K9 (VSS), U24.2 (GND), U25.3 (NC), U25.4 (NC), U25.6 (NC), U25.8 (NC), U25.9 (GND), U26.7 (GND), U27.3 (GND), U28.2 (GND), U30.2 (GND), U31.2 (GND), U32.1 (GND), U33.6 (~E), U33.7 (VEE), U33.8 (GND), U34.3 (GND), U35.3 (GND), U36.3 (GND), U37.2 (GND), U38.7 (GND), U39.3 (GND), U40.7 (GND), X1.2 (GND), X2.2, X2.4
unnamed: C13.1, R1.1, R2.2
unnamed: C15.2, R3.2
unnamed: C45.2, R26.1
unnamed: C50.2, R152.1
unnamed: C54.1, L8.1, L14.2
unnamed: C56.1, L14.1, L15.2
unnamed: C67.1, R150.1
unnamed: C78.2, R115.2
unnamed: C91.2, C101.1, L16.1
unnamed: C101.2, C103.1, L18.1
unnamed: C96.1, C103.2, L17.1
unnamed: C112.1, R35.2
unnamed: C112.2, L13.1, L19.2
unnamed: C115.1, R149.1
unnamed: C139.1, L12.1, L26.2, R128.1, R129.2
unnamed: C139.2, R131.2
unnamed: C188.1, C189.2, R155.2
unnamed: C191.1, L27.2, L28.1, R132.1, R133.2
unnamed: C191.2, R130.2
unnamed: C192.2, R134.2
unnamed: C195.1, L33.2, L34.1, R137.1, R138.2
unnamed: C195.2, R136.2
unnamed: C198.2, R142.2
unnamed: C202.1, R147.1
unnamed: C202.2, L2.2, L3.1, R124.1, R144.1
unnamed: C203.1, L29.2, L30.1, R43.1, R142.1
unnamed: C203.2, R143.2
unnamed: C207.1, L5.2, L32.1, R117.1, R154.2
unnamed: C207.2, R146.2
unnamed: C210.1, L4.2, L31.1, R116.1, R153.2
unnamed: C210.2, R42.2
unnamed: C211.2, R123.2
unnamed: C64.2, D1.1 (A1), L13.2, P3.1 (RF)
unnamed: D2.2 (A), R18.1, TP10.1
unnamed: D4.1 (A1), R72.1, TP12.1
unnamed: D4.3 (A2), R125.1, TP11.1
unnamed: D5.2 (A), R73.1, TP13.1
unnamed: D6.3 (A2), R74.1, TP14.1
unnamed: D7.1 (A1), R75.1, TP8.1
unnamed: D7.3 (A2), R50.1, TP7.1
unnamed: D8.1 (A1), R76.1, TP9.1
unnamed: C171.1, D10.2 (A), U24.6 (OUT)
unnamed: C143.1, D11.1 (K), D12.1 (K), D13.1 (K), FB1.2
unnamed: D13.2 (A), Q5.3 (D)
unnamed: C64.1, C68.2, D14.1 (K), D15.2 (A)
unnamed: C69.1, D15.1 (K), Q1.6 (D), R29.1
unnamed: D16.2 (A), R89.1
unnamed: D16.1 (K), R81.2, R86.1, R88.2
unnamed: D17.2 (A), R91.1
unnamed: D17.1 (K), R83.2, R87.1, R90.2
unnamed: FL2.1 (IN), U2.11 (RF3)
unnamed: FL3.1 (IN), U2.9 (RF4)
unnamed: JP1.1 (A), U23.L14 (P6_5)
unnamed: L6.1, R144.2
unnamed: L21.1, R110.2
unnamed: L22.1, R111.2
unnamed: L23.1, R102.2
unnamed: L24.1, R112.2
unnamed: Q1.3 (D), R29.2
unnamed: C153.2, FB3.1, Q3.3 (D)
unnamed: C153.1, Q3.1 (G), R11.2, R60.1
unnamed: Q4.1 (G), Q9.6 (C1), R22.1, R58.2
unnamed: Q5.1 (G), Q9.3 (C2), R57.1, R70.2
unnamed: C180.2, FB4.1, Q6.3 (D)
unnamed: C180.1, Q6.1 (G), R61.2, R71.1
unnamed: Q7.2 (B1), R53.2
unnamed: Q7.6 (C1), R71.2
unnamed: Q9.2 (B1), R81.1
unnamed: Q9.5 (B2), R83.1
unnamed: Q10.2 (B1), R77.1, R79.1
unnamed: Q10.6 (C1), R86.2
unnamed: Q10.5 (B2), R78.1, R80.1
unnamed: Q10.3 (C2), R87.2
unnamed: R19.2, R49.2, SW2.1, TP30.1
unnamed: R24.2, R92.1, U26.2, U26.12
unnamed: R7.1, R30.2, SW1.1, TP31.1
unnamed: R94.2, R95.1, U26.5, U27.1
unnamed: R96.2, R97.1, U26.10, U26.13
unnamed: R98.2, R99.1, U11.2, U27.2
unnamed: R108.2, U31.4
unnamed: C28.1, T1.1 (S1)
unnamed: C25.1, T1.2 (S2)
unnamed: C46.2, T2.1 (S1)
unnamed: C49.2, T2.2 (S2)
unnamed: C51.1, L8.2, U1.11 (RF3)
unnamed: C91.1, U1.9 (RF4)
unnamed: C107.2, L22.2, U3.5 (D1+)
unnamed: C107.1, L21.2, U3.4 (D1-)
unnamed: C14.2, R3.1, U4.6 (LFILT1)
unnamed: C14.1, C15.1, R2.1, U4.7 (LFILT2)
unnamed: C12.1, R1.2, U4.8 (LFILT3)
unnamed: R120.2, U4.9 (MODE/GPO6)
unnamed: R4.2, U4.4 (REXT)
unnamed: C211.1, U5.3 (RF1)
unnamed: C108.1, R110.1, U8.7 (D2+)
unnamed: C108.2, R111.1, U8.6 (D2-)
unnamed: C96.2, U9.3 (RF1)
unnamed: C61.1, L15.1, U9.2 (RF3)
unnamed: C68.1, U14.4 (ANT)
unnamed: R145.2, U16.14 (IOB_32a_SPI_SO)
unnamed: C106.1, U17.33 (BYPASS)
unnamed: C83.1, R121.2, R122.1, U18.46 (REFIN)
unnamed: C125.2, R46.2, R47.2, U21.1 (ADJ2)
unnamed: R55.2, R56.2, U21.5 (DEF_1)
unnamed: R52.2, U21.7 (EN1)
unnamed: L11.2, U21.6 (SW1)
unnamed: L10.1, U21.10 (SW2)
unnamed: R140.1, U23.P2 (P1_4)
unnamed: R141.1, U23.N9 (P1_19)
unnamed: R6.1, U23.J14 (P2_6)
unnamed: R37.1, R82.2, U23.B2 (P4_3)
unnamed: R107.1, U23.B1 (P4_6)
unnamed: R127.2, U23.P9 (PD_12)
unnamed: R20.1, U24.5 (ILIM)
unnamed: C59.2, U25.2 (RFIN)
unnamed: C62.1, L12.2, R129.1, U25.7 (RFOUT)
unnamed: R101.1, U28.5 (ILIM)
unnamed: U30.4, U31.1
unnamed: R33.1, U33.3 (A)
unnamed: C74.1, R102.1, U34.7 (D2+)
unnamed: C74.2, R112.1, U34.6 (D2-)
unnamed: C76.2, L24.2, U35.5 (D1+)
unnamed: C76.1, L23.2, U35.4 (D1-)
unnamed: R135.1, U38.6 (ADJ)
unnamed: C194.1, L33.1, R137.2, U38.2 (BIAS)
unnamed: L34.2, R123.1, R134.1, R138.1, U38.3 (RFIN)
unnamed: C192.1, L28.2, R133.1, R155.1, U38.4 (RFOUT)
unnamed: R114.1, U40.6 (ADJ)
unnamed: C53.1, L4.1, R116.2, U40.2 (BIAS)
unnamed: C58.2, L31.2, R115.1, R153.1, U40.3 (RFIN)
unnamed: C78.1, L32.2, R152.2, R154.1, U40.4 (RFOUT)
unnamed: C155.2, X1.3 (OUT)
SCL: P22.26, R28.2, U19.4 (SCL), U23.K13 (I2C0_SCL)
SDA: P22.24, R27.2, U19.5 (SDA), U23.K14 (I2C0_SDA)
SSP1_CIPO: R145.1, TP53.1, U23.M2 (P1_3)
SSP1_COPI: R140.2, TP52.1, U16.17 (IOB_33b_SPI_SI), U17.19 (DIN), U18.34 (DIN)
SSP1_SCK: R141.2, TP51.1, U16.15 (IOB_34a_SPI_SCK), U17.18 (SCLK), U18.35 (SCLK)
VAA: C1.1, C2.1, C3.1, C5.1, C22.1, C41.1, C42.1, C48.1, C52.1, C71.1, C72.1, C73.1, C75.1, C77.1, C79.1, C82.1, C84.1, C85.1, C86.1, C87.1, C88.1, C89.1, C90.1, C92.1, C93.1, C94.1, C105.1, C141.1, C142.1, C154.1, C156.1, C159.1, C160.1, C161.1, C162.1, C190.1, C193.1, C200.1, C201.1, C204.1, C206.1, C208.1, C212.1, FB3.2, L2.1, L5.1, L26.1, L27.1, L29.1, R5.1, R18.2, R36.2, R114.2, R117.2, R120.1, R121.1, R128.2, R132.2, R135.2, TP4.1, U3.9 (V+), U4.5 (ANA_VDD1), U4.19 (DIG_VDD), U4.22 (ANA_VDD2), U8.9 (V+), U13.1, U13.5 (VCC), U17.1 (VCCLNA), U17.7 (VCCPA), U17.13 (VCCTXPA), U17.17 (VCCTXMX), U17.20 (VCCPLL), U17.25 (VCCCP), U17.27 (VCCXTAL), U17.30 (VCCVCO), U17.39 (VCCRXVGA), U17.41 (VCCRXFL), U17.46 (VCCRXMX), U18.2 (VDD), U18.8 (VDD), U18.11 (VDD), U18.33 (VDD), U18.39 (VDD), U18.43 (VDD), U24.1 (IN), U25.1 (VCC), U32.3 (VI), U34.9 (V+), U35.9 (V+), U36.1, U36.5 (VCC), U38.1 (VCC), U39.5 (VCC), U40.1 (VCC)
VCC: C33.1, C39.1, C40.1, C43.1, C128.1, C129.1, C130.1, C131.1, C132.1, C133.1, C134.1, C135.1, C137.1, C138.1, C144.1, C145.2, C146.2, C165.1, C169.1, FB5.1, L11.1, P26.1, Q6.2 (S), R27.1, R28.1, R38.1, R48.1, R56.1, R59.1, R61.1, R63.2, R64.2, R66.1, R67.2, R100.2, TP19.1, U20.8 (VCC), U21.4 (FB1), U23.A6 (VDDA), U23.D8 (VDDREG), U23.E3 (USB0_VDDA3V3_DRIVER), U23.E8 (VDDREG), U23.F3 (USB0_VDDA3V3), U23.G10 (VDDIO), U23.H5 (VDDIO), U23.H10 (VDDIO), U23.K8 (VDDIO), U28.1 (IN), U30.5 (V+), U31.5 (V+), U33.16 (VCC)
